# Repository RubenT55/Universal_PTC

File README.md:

# Universal PTC Board

A PCB project designed in **KiCad 9.0** that implements an external, universal PTC (Positive Temperature Coefficient) circuit for CRT monitors.

## Description
Many modern generic replacement chassis for CRT monitors (commonly known as "universal Chinese chassis") do not include an integrated PTC circuit to perform the automatic degaussing function of the screen. 

This board provides a compact, external solution, allowing you to add the degaussing feature cleanly and safely. It is designed to be compatible with most CRT picture tubes and generic arcade/TV chassis on the market.

## Repository Contents
- `UniversalPTC.kicad_pro` — Main KiCad project file
- `UniversalPTC.kicad_sch` — Schematic design
- `UniversalPTC.kicad_pcb` — PCB layout
- `local_libs/` — Directory containing project-specific assets
  - `3dmodels/` — 3D component models (e.g., MZ73 connectors) in `.step` format
  - `footprints/` — Custom footprint libraries (`.pretty`)
  - `symbols/` — Custom schematic symbols (`.kicad_sym`)

## Requirements
- [KiCad 9.0](https://www.kicad.org/) or higher.

## How to open the project
1. Clone the repository to your local machine:
   `git clone https://github.com/RubenT55/Universal_PTC.git`
2. Open KiCad, go to **File > Open Project**, and select the `UniversalPTC.kicad_pro` file.

> **Technical note:** This project is 100% *portable*. All custom footprints, symbols, and 3D models (like the PTC connector) are isolated inside the `local_libs/` folder using relative paths (`${KIPRJMOD}`). There is no need to install external libraries or configure global environment variables to view the complete project, including the 3D viewer.

## License
This project is open source. Feel free to modify, manufacture, and adapt the board for your arcade and CRT restoration needs.

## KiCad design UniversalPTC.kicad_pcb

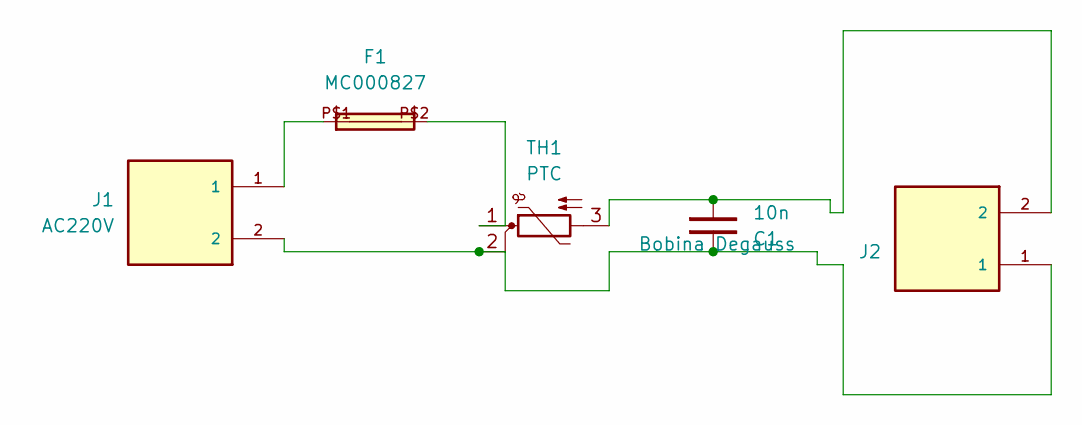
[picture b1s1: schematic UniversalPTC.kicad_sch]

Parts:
C1: 10n; C_Rect_L13.5mm_W5.0mm_P10.00mm_FKS3_FKP3_MKS4
F1: MC000827
J1: AC220V; HANDSON_KF301-2P; PARTREV NA
J2: Bobina Degauss; HANDSON_KF301-2P; PARTREV NA
TH1: PTC; PTC_MZ73-B_Degauss_Pitch2.5_5.0

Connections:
unnamed: C1.1, J2.2, TH1.3
unnamed: C1.2, J1.2, J2.1, TH1.2
unnamed: F1.P$1, J1.1
unnamed: F1.P$2, TH1.1

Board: 2 copper layers, 5 parts (0 on the bottom side), 4 nets, no tracks yet.

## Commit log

2026-03-03 Estructura aislada en C: con librerias y modelos 3D locales
2026-03-03 Eliminados los plugins del repositorio para ahorrar espacio
2026-03-03 Create README.md for Universal PTC Board project
    Added README.md with project details and instructions.
